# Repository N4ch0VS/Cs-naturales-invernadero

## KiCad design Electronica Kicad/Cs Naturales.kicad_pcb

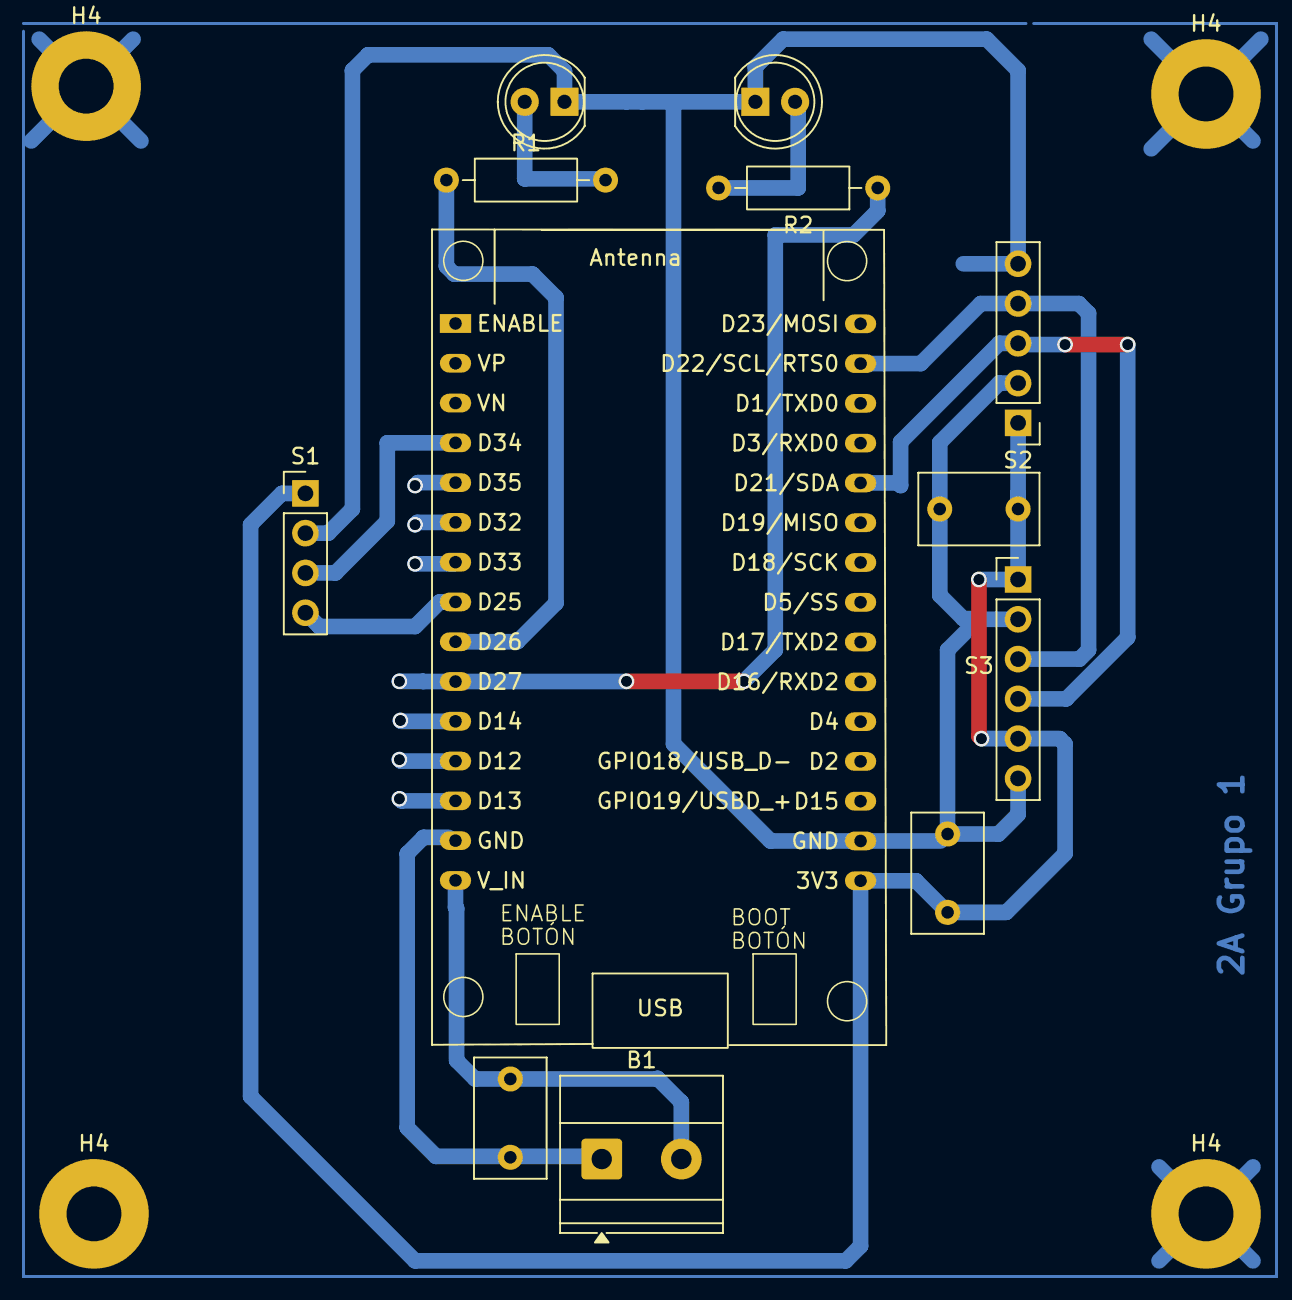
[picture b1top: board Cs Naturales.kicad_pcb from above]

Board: 2 copper layers, 13 parts (0 on the bottom side), 12 nets.

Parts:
B1: 9V; TerminalBlock_Phoenix_MKDS-1,5-2-5.08_1x02_P5.08mm_Horizont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
D1: LED_ON; LED_D5.0mm
D2: LED_Internet; LED_D5.0mm_Clear
H4, H4#2, H4#3, H4#4: Sujeción; MountingHole_3.5mm_Pad
M1: ESP32-DevKit_V1
R1, R2: 220; R_Axial_DIN0207_L6.3mm_D2.5mm_P10.16mm_Horizontal
S1: Conn_01x04_MountingPin; PinHeader_1x04_P2.54mm_Vertical
S2: Conn_01x05_MountingPin; PinHeader_1x05_P2.54mm_Vertical
S3: Conn_01x06_MountingPin; PinHeader_1x06_P2.54mm_Vertical

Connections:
GND: D1.1 (K), D2.1 (K), M1.17 (GND), S1.2, S2.2, S2.5, S3.2, S3.6
GND_In: B1.1, M1.14 (GND)
LED_ON: M1.10 (D27/ADC2_7/T7/~), R2.1
LED_WIFI: M1.9 (D26/ADC2_9/DAC2/~), R1.1
unnamed: D1.2 (A), R2.2
unnamed: D2.2 (A), R1.2
S1 +: H4#4.1, M1.16 (3v3), S1.1, S2.1, S3.1, S3.5
S1 A0: M1.8 (D25/ADC2_8/DAC1/~), S1.4
S1 D0: M1.4 (D34/ADC1_6), S1.3
S2 SCL: M1.29 (D22/SCL/V_SPI_WP/RTS0/~), S2.4, S3.3
S2 SDA: M1.26 (D21/SDA/VSPI_HD/~), S2.3, S3.4
Vin: B1.2, M1.15 (Vin(hasta12v))

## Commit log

2025-09-02 Archivos Kicad
2025-09-02 Archivos electronica
2025-09-03 archivo node-red
2025-09-03 Remove submodule Cs-naturales-invernadero
2025-09-03 Correcion archivo
2025-09-03 Modifico Archivo Esquematico y agrego ESP32 MOD
2025-09-09 Modifico archivo Kicad
2025-09-10 Diseño PCB listo
2025-09-23 Add files via upload
    json 23/09
2025-10-10 PCB Terminada
2025-10-17 Flow funcional
2025-10-21 Ordenado
